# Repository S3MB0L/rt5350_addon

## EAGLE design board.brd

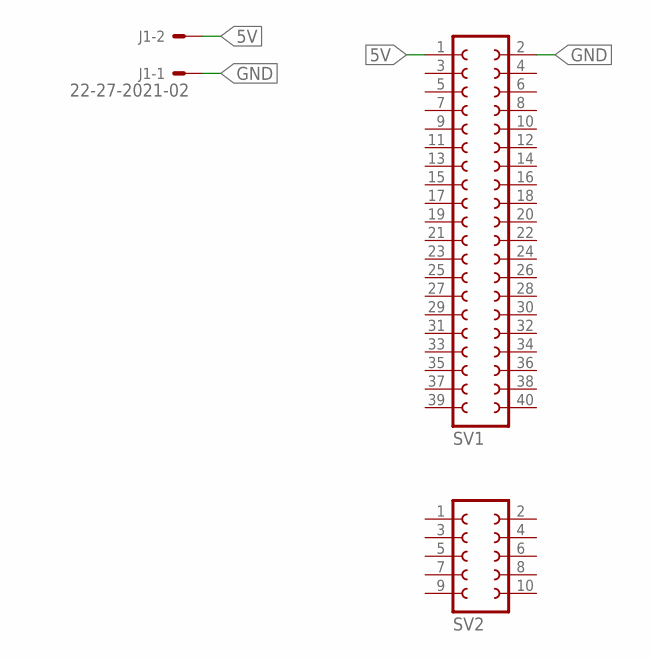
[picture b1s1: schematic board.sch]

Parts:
J1: 22-27-2021-02; 6410-02
SV1: FE20-2
SV2: FE05-2

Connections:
5V: J1.2, SV1.1
GND: J1.1, SV1.2

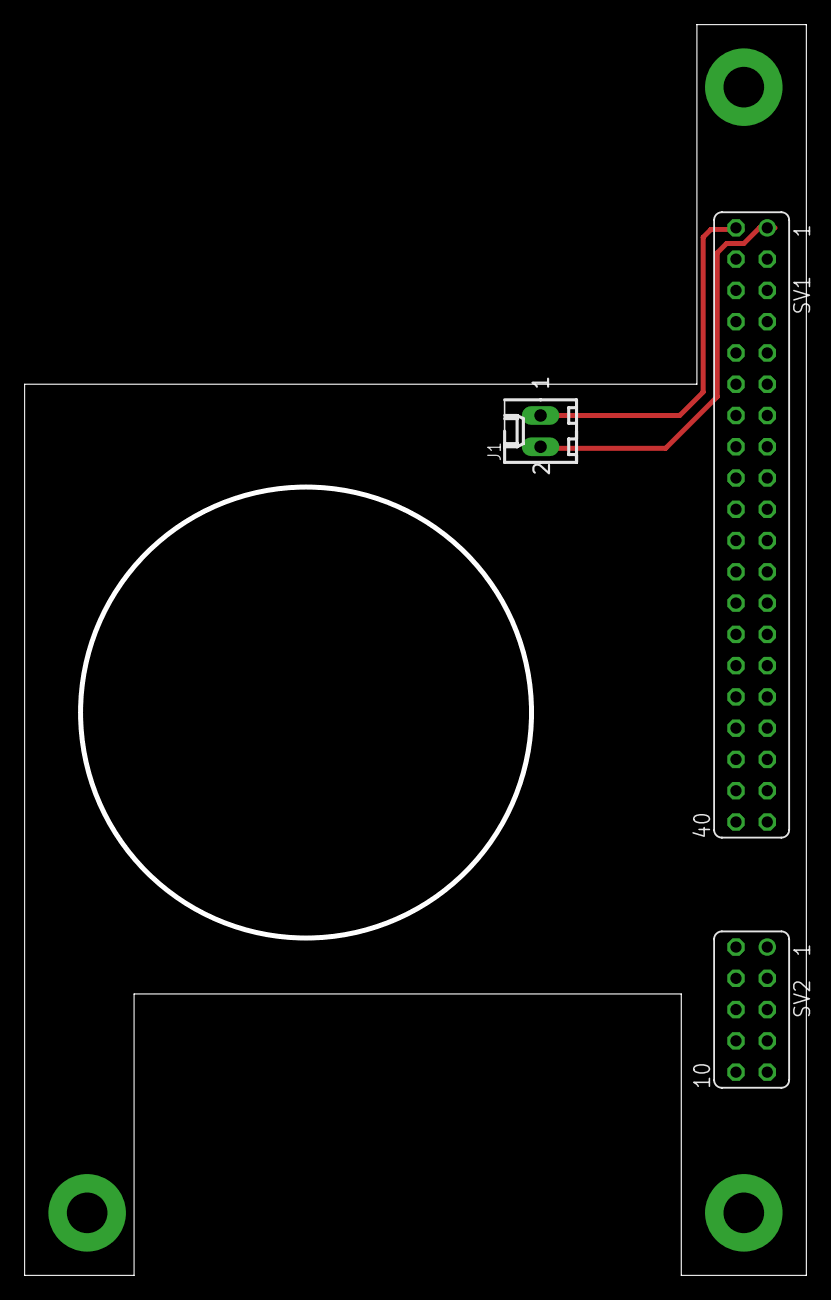
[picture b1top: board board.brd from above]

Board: 2 copper layers, 63.5 x 101.6 mm, 3 parts (0 on the bottom side), 2 nets.
